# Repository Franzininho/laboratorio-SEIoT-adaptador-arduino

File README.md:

## Adaptador para Arduino - Placa Laboratório de Sistemas Embarcados e IoT

## O que é este projeto?

Este projeto é um adaptador que permite a conexão da placa Arduino Uno com a placa [Laboratório de Sistemas Embarcados e IoT](https://github.com/Franzininho/laboratorio-SEIoT-Franzininho-Wifi) através de uma correspondência entre os pinos do Arduino Uno e a pinagem da Franzininho Wifi (placa utilizada no projeto da placa de laboratório). Para utilizar o adaptador basta conectá-lo ao Arduino como um shield e então conectar o adaptador na placa. 

Esse projeto está sob a licença [CERN-OHL-S v2](https://ohwr.org/cern_ohl_s_v2.txt)

## Codificação dos pinos de ativação

Como a placa [Laboratório de Sistemas Embarcados e IoT](https://github.com/Franzininho/laboratorio-SEIoT-Franzininho-Wifi) conta com um sistema de codificação dos pinos de ativação dos periféricos, foi preciso codificar esses pinos. A codificação escolhida tem dois algarismos sendo que o primeiro indica a funcionalidade do pino e o segundo indica uma numeração do pino.

O código de cada pino está impresso ao lado dele na placa principal e para facilitar a utilização do adaptador foi impresso nele a correspondência entre o pino do Arduino e o código de ativação na placa. Essa correspondência também pode ser acessada [clicando aqui](./informacoes/mapeamento.md).

Além disso, também foi desenvolvida uma biblioteca para uso em conjunto com o placa que permite o uso dos códigos dos pinos de ativação dentro da programação. [Clique aqui](https://github.com/Franzininho/biblioteca-laboratorioFW_ARDUNO) para acessar a **biblioteca laboratorioFW_ARDUNO.**

## Como o projeto foi desenvolvido?

O projeto foi desenvolvido com o software [KiCad 7](https://www.kicad.org/). Esse software é aberto e está disponível para Linux, MacOS e Windows.

## Certificação OSHWA

[Clique aqui](https://certification.oshwa.org/br000013.html) para acessar

---

#### Feito por [LelePG](https://github.com/LelePG)

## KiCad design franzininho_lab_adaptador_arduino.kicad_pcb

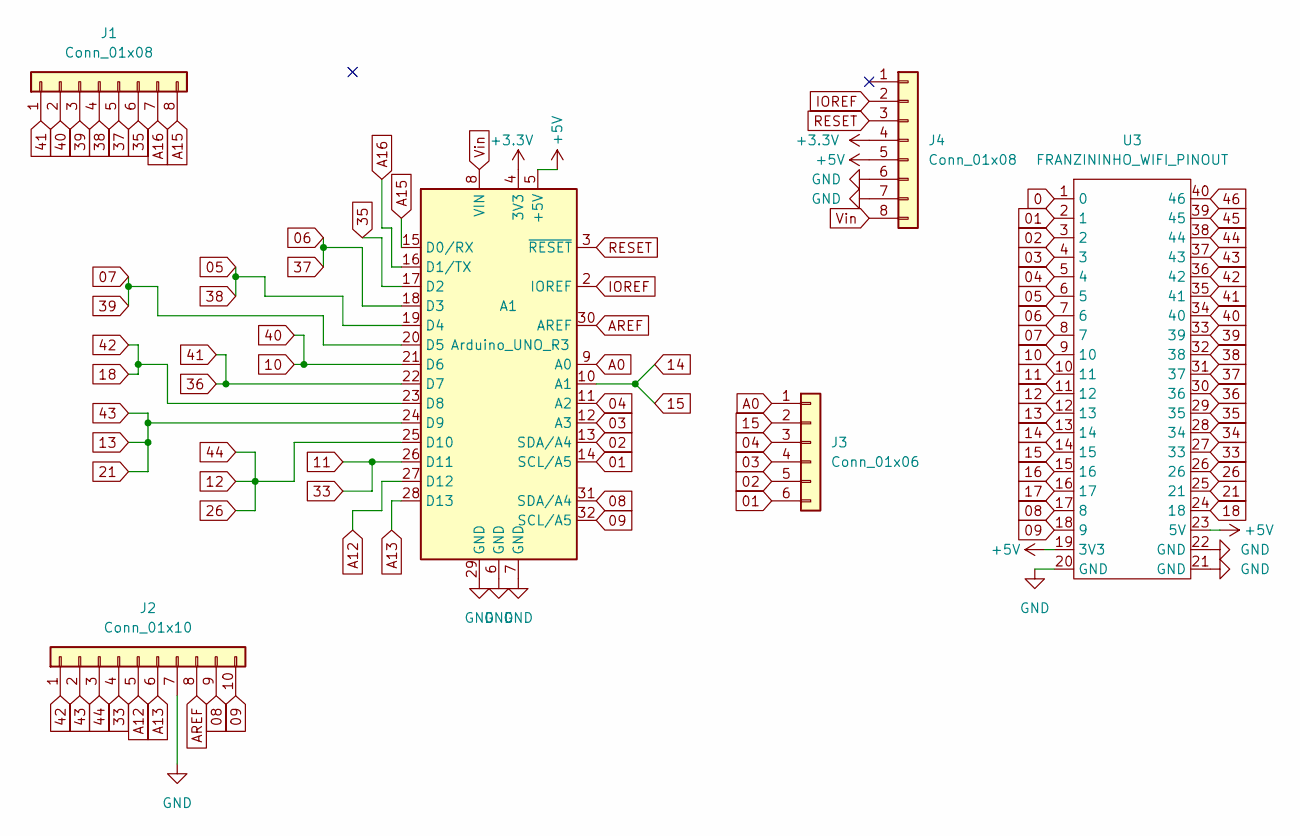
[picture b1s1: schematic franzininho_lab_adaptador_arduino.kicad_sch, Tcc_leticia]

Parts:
A1: Arduino_UNO_R3
J1, J4: Conn_01x08; PinHeader_1x08_P2.54mm_Vertical
J2: Conn_01x10; PinHeader_1x10_P2.54mm_Vertical
J3: Conn_01x06; PinHeader_1x06_P2.54mm_Vertical
U3: FRANZININHO_WIFI_PINOUT

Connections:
0: U3.1 (0)
01: A1.14 (SCL/A5), J3.6, U3.2 (1)
02: A1.13 (SDA/A4), J3.5, U3.3 (2)
03: A1.12 (A3), J3.4, U3.4 (3)
04: A1.11 (A2), J3.3, U3.5 (4)
05: A1.19 (D4), J1.4, U3.6 (5), U3.32 (38)
06: A1.18 (D3), J1.5, U3.7 (6), U3.31 (37)
07: A1.20 (D5), J1.3, U3.8 (7), U3.33 (39)
08: A1.31 (SDA/A4), J2.9, U3.17 (8)
09: A1.32 (SCL/A5), J2.10, U3.18 (9)
10: A1.21 (D6), J1.2, U3.9 (10), U3.34 (40)
11: A1.26 (D11), J2.4, U3.10 (11), U3.27 (33)
12: A1.25 (D10), J2.3, U3.11 (12), U3.26, U3.38 (44)
13: A1.24 (D9), J2.2, U3.12 (13), U3.25 (21), U3.37 (43)
14: A1.10 (A1), J3.2, U3.13 (14), U3.14 (15)
16: U3.15 (16)
17: U3.16 (17)
18: A1.23 (D8), J2.1, U3.24 (18), U3.36 (42)
34: U3.28 (34)
35: A1.17 (D2), J1.6, U3.29 (35)
36: A1.22 (D7), J1.1, U3.30 (36), U3.35 (41)
45: U3.39 (45)
46: U3.40 (46)
+3.3V: A1.4 (3V3), J4.4
+5V: A1.5 (+5V), J4.5, U3.19 (3V3), U3.23 (5V)
A0: A1.9 (A0), J3.1
A12: A1.27 (D12), J2.5
A13: A1.28 (D13), J2.6
A15: A1.15 (D0/RX), J1.8
A16: A1.16 (D1/TX), J1.7
AREF: A1.30 (AREF), J2.8
GND: A1.6 (GND), A1.7 (GND), A1.29 (GND), J2.7, J4.6, J4.7, U3.20 (GND), U3.21 (GND), U3.22 (GND)
IOREF: A1.2 (IOREF), J4.2
RESET: A1.3 (~RESET), J4.3
Vin: A1.8 (VIN), J4.8

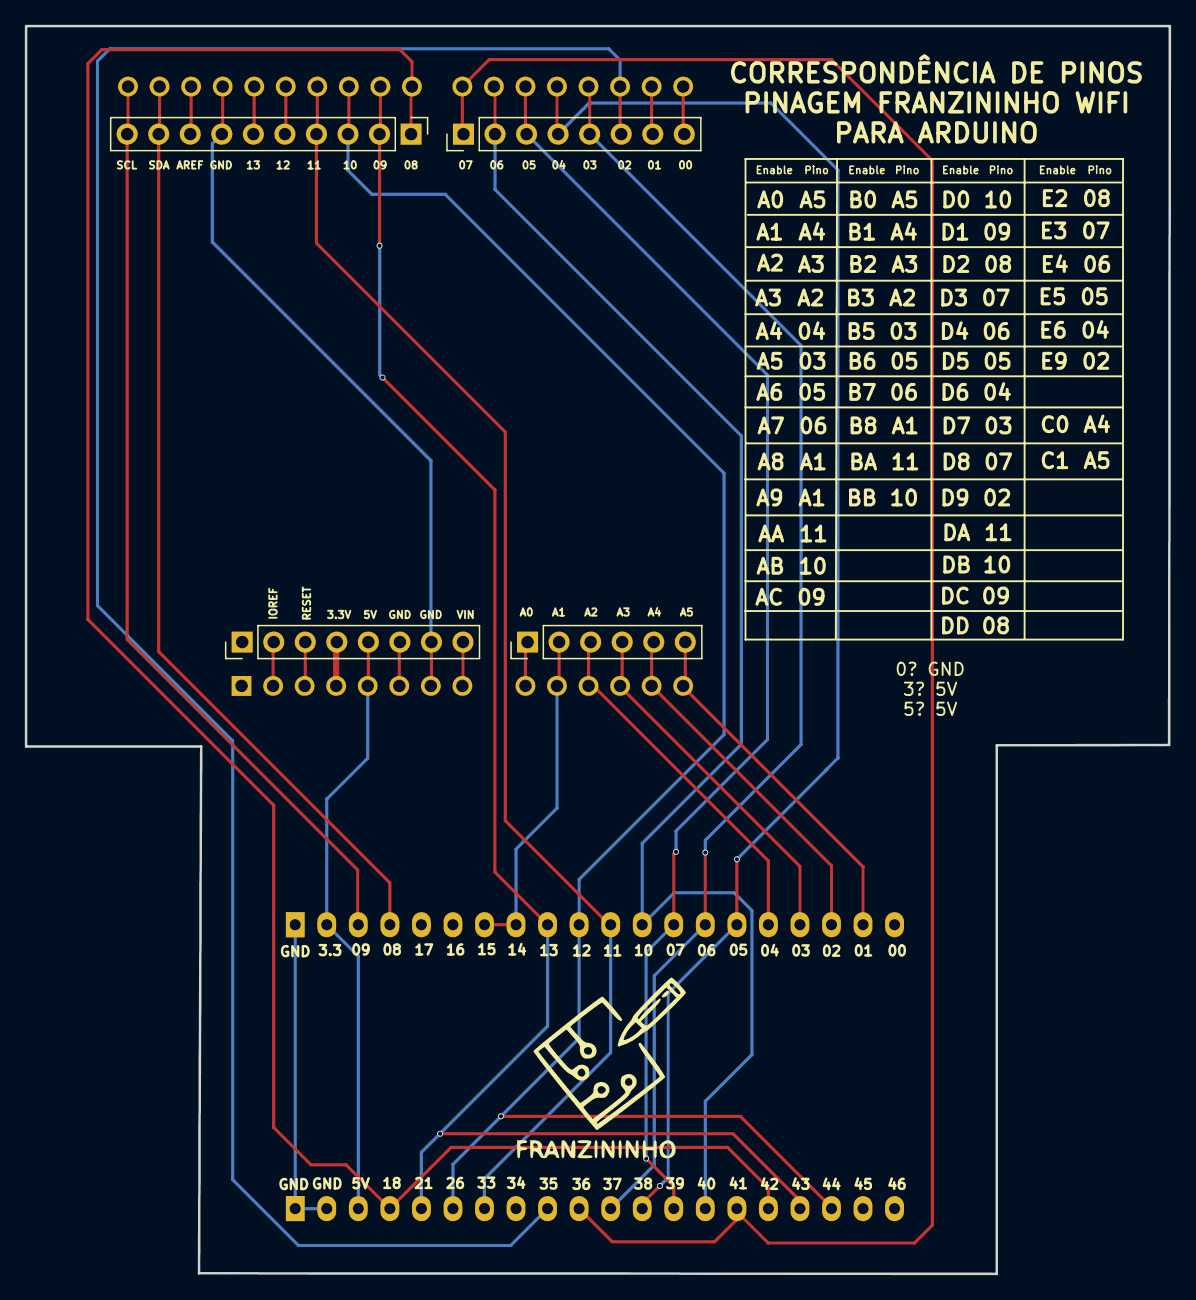
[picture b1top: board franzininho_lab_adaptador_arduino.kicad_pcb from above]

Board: 2 copper layers, 92.1 x 100.5 mm, 6 parts (1 on the bottom side), 29 nets.

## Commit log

2023-03-25 primeiro commit
2023-03-25 correção de nomenclatura
2023-05-13 adição de licensa
2023-05-20 Update README.md
    continuo dando uma olhada nos readme :)
2023-05-23 adicionada certificação OSHWA
